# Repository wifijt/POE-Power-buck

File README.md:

# FRC PoE-switch 12 V buck-boost

A small 4-layer board that takes FRC robot power (a PDH/PDP breaker slot) and
holds a steady **12.1 V** for a Linovision **POE-Switch0504GDF**
(4-port gigabit PoE, DC 9-57 V input). It keeps the switch and its PoE cameras or
coprocessors alive when the battery sags below 9 V under heavy drive load.

| | |
|---|---|
| Board | 36.0 x 57.0 mm, 4 layers, 1.6 mm, 1 oz outer copper, rounded corners |
| Mounting | 3x M3 (3.2 mm, non-plated, no copper within 3.3 mm): top-left at (2.9, 3.4) mm, bottom corners at (3.5, 53.4) and (32.5, 53.4) mm from the top-left corner. Isolated from every net, as FRC requires for the robot frame |
| Input | 6-16 V (starts at ~5.5 V rising, stops at ~5.0 V; 16 V TVS clamp), reverse-polarity protected |
| Output | 12.1 V, 5 A continuous (60 W). Full power down to about 5.3 V input (14.9 A typ / 12.7 A min average inductor-current limit) |
| Converter | TI **TPS552882** 4-switch buck-boost (standalone, no I2C), 400 kHz |
| Connectors | 2x **WAGO 2604-3102** lever terminals (5.0 mm, up to 12 AWG / 4 mm²). Vertical wire entry; levers face the top edge |
| Indicator | Green LED = 12 V output present |

Silkscreen, left to right along the top edge: **OUT 12V (+ -)** then **IN (+ -)**.

## Wiring on the robot

* **IN**: from a PDH/PDP channel through a **10-20 A breaker**, 14-16 AWG.
* **OUT**: to the switch's PWR1 terminal (9-57 V). The switch's PoE budget is 60 W at
  12 V input (Linovision datasheet), so keep total PoE load plus the switch's own draw under about 55 W.
* The output's `-` is the board's ground, behind the reverse-polarity FET. Don't tie it to the
  input `-` anywhere else.

## Ordering (JLCPCB PCB + assembly)

1. **PCB**: upload `fab/gerbers_JLCPCB.zip` with these options:
   * Layers: **4**, thickness **1.6 mm**
   * Outer copper weight: **1 oz** (default). Inner copper weight: 0.5 oz (default)
   * Surface finish: ENIG recommended for the 0.5 mm-pitch U1 pads (HASL also works). Impedance control: off
   * **Via covering: Epoxy Filled & Capped** (a paid option on 4 layers). U1 has six 0.2 mm-drill
     vias inside its PGND and VOUT center pads; open vias there would wick solder away from the QFN.
     Set **min via hole size to 0.2 mm** (0.35 mm diameter) in the quote.

   1 oz outer copper is enough for the planned 40-55 W load (two Raspberry Pi 5s and an
   Orange Pi 5 on PoE). VIN, VOUT and GND each have a full inner plane alongside the top pour, and
   the top-only runs (GND_IN, SW1, SW2) are short: about a 10 °C rise at 12 V in, about 35 °C only
   with a sustained 6 V input. Avoid 2 oz: JLC then asks for a 0.254 mm annular ring on plated
   holes, and this board's vias have 0.15 mm (0.6/0.3) and 0.075 mm (0.35/0.2 via-in-pad) rings.
2. **Assembly**: top side only. Upload `fab/BOM_JLCPCB.csv` and `fab/CPL_JLCPCB.csv`.
   * Every line has a JLCPCB/LCSC part number, taken from jlcpcb.com part pages (Nov 2026).
     Stock changes daily, so re-run JLC's matching before you pay and swap anything out of stock
     for the same value, package and voltage rating.
   * Stock was checked against JLC's live matching on 2026-11-11. Two lines had none, so they
     were swapped: C1/C20 are now the MA35V100M6X8 polymer (C46550467, 100 µF 35 V, 30 mΩ,
     Economic OK) instead of EEH-ZK1V101XP (C454360), and R9 is now UniOhm 0402WGF2672TCE (C25876).
     Fallback for C1/C20: Lelon HBV101M1VTR-0608 hybrid (C967098). L1 (C41422303) and
     Q1-Q3 (C201632) have only a few hundred in stock.
   * Rotations were checked in JLC's placement preview (2026-11-10). C1/C20 needed 180° and
     `gen_fab.py` now applies that; U1, Q1-Q3 and D1-D3 match. Still glance at the preview: the
     magenta **+** on C1/C20 must sit on the bottom pad, next to the white silkscreen **+**.
3. **Hand-solder** J1 and J2 (WAGO 2604-3102, `fab/BOM_hand_solder.csv`) after the board
   arrives. The pads are 2.6 mm with 1.4 mm drills, two pins per pole, and are connected solid to
   the copper planes, so use a big iron tip.

## First power-up

0. Before any power, check D1 (the SMBJ16A TVS) isn't reversed: meter in diode mode, red probe on
   OUT - (board GND), black on IN +. Expect ~0.6-0.7 V; swapped probes read open (or C1 charging).
   ~0.6 V with red on IN + means D1 is backwards and would short the input.
1. Bench supply at 12 V with a 0.5 A current limit and no load. Expect 12.1 V (±2 %) and the LED on.
2. Sweep the input from 6 V to 16 V with a 1-2 A load and check the output stays at 12 V.
3. Raise the load step by step to 5 A at 12 V input, then at 7 V input. Watch the temperatures of
   L1, Q1 and Q2 (the buck-leg FETs) and U1.
4. Reverse the input briefly at a low current limit and confirm nothing conducts.

## What's in here

```
frc-poe-buckboost.kicad_pro / .kicad_sch / .kicad_pcb   KiCad 10 project
frc_poe.pretty/      TPS552882 VQFN-HR-26, WAGO 2604-3102, NexFET SON3x3 footprints
enclosure/           3D-printable case (OpenSCAD source + tray/lid STLs), see enclosure/README.md
fab/                 Gerbers + drill (zip), JLC BOM, JLC CPL, hand-solder BOM
docs/                schematic.pdf, board_top.png, board_layers.png,
                     TPS552882_datasheet_SLVSFC5.pdf (TI, Nov 2020; the design notes cite it)
scripts/             generators - design.py is the single source of truth
```

Regenerate everything after editing `scripts/design.py`. The PCB scripts need KiCad's own
Python (the one that can `import pcbnew`). Tested with KiCad 10.0.6 on macOS; the scripts also
still handle KiCad 7 on Linux (`/usr/bin/python3`, libraries in `/usr/share/kicad`). Set
`KICAD_SHARE` if the stock symbol/footprint libraries live somewhere else.

```bash
KPY=/Applications/KiCad/KiCad.app/Contents/Frameworks/Python.framework/Versions/3.9/bin/python3
KCLI=/Applications/KiCad/KiCad.app/Contents/MacOS/kicad-cli

python3 scripts/gen_footprints.py
python3 scripts/gen_sch.py
$KPY scripts/gen_pcb.py            # placement, tracks, zones (unfilled)
$KPY scripts/fill_drc.py           # reload, fill zones, save, DRC report -> drc.rpt
$KPY scripts/gen_fab.py            # BOM / CPL / hand-solder BOM

# gerbers + drill -> fab/gerbers_JLCPCB.zip
rm -f fab/gerbers/* fab/gerbers_JLCPCB.zip
$KCLI pcb export gerbers -o fab/gerbers/ --use-drill-file-origin \
  -l F.Cu,In1.Cu,In2.Cu,B.Cu,F.Paste,F.Silkscreen,B.Silkscreen,F.Mask,B.Mask,Edge.Cuts frc-poe-buckboost.kicad_pcb
$KCLI pcb export drill -o fab/gerbers/ --drill-origin plot --format excellon -u mm --excellon-separate-th frc-poe-buckboost.kicad_pcb
(cd fab/gerbers && zip -q ../gerbers_JLCPCB.zip *)

# check the schematic against design.py
$KCLI sch export netlist -o /tmp/frc.net frc-poe-buckboost.kicad_sch
python3 scripts/check_netlist.py /tmp/frc.net
```

KiCad 10 notes: the `pcbnew` scripts print harmless wxWidgets assert lines. Don't call
`pcbnew.WriteDRCReport()` from a script; it segfaults outside the GUI, which is why
`fill_drc.py` runs DRC through `kicad-cli`.

## Design notes

* **Copper**: 1 oz outer layers, 0.2 mm minimum track and clearance throughout (more than JLC's 1 oz minimum).
* **Layers**: top = parts, switch-node and power pours. Inner 1 = solid GND. Inner 2 = VOUT
  plane (left) and VIN plane (right). Bottom = GND plus the DR1H and EN traces.
* **U1 grounding** (TI SLVSFC5 sec. 10.1): three filled-and-capped vias in each of U1's center pads
  (PGND to the In1 ground plane, VOUT to the In2 VOUT plane) for heat and current. Analog ground
  (U1 AGND and MODE pins, R7, R9, C12 and C13) is its own AGND net, routed as traces and joined
  to power ground only at C14's ground terminal through net tie NT1. R4, R5 and C11 stay on the
  main ground plane.
* **Reverse polarity**: Q3 (low-side N-FET, gate from VIN through R12, 12 V zener clamp D3).
* **Values** (FB 100k/11k = 12.1 V; the reference used 102k/11.3k, FSW 49.9k, ILIM 22.1k (was 26.7k), UVLO 100k/28.7k (was 26.1k), compensation 15k + 10 nF + 100 pF, VCC 22 µF,
  6.8 µH inductor, external CSD17577Q3A buck FETs) follow two published TPS552882/TPS55288
  designs: a 12 V output stage in EwoudVV/ducktop2 and a 16 A booster in
  mikegoelzer/Homebrew-ECP5-SBC. The output bulk (100 µF hybrid + 4x 22 µF) is at least what
  the 12 V reference uses, which keeps the boost-mode right-half-plane zero well above crossover.
* **Checks done**: the schematic netlist, the PCB pad nets and `design.py` all match. KiCad DRC
  reports 0 unconnected items and 0 clearance errors. What's left is courtyard overlap between
  deliberately tight parts (hot-loop caps next to the FETs, boot cap next to U1) and silkscreen
  clipping.
* **Checked against TI's TPS552882 datasheet (SLVSFC5, Nov 2020)**: all 26 pins, the RPM0026A
  land pattern (pads match TI's example layout to <0.005 mm), and the FB, FSW, ILIM, EN/UVLO,
  MODE, DITH, VCC and bootstrap values. Two values changed as a result: R9 26.7k -> 22.1k (the
  old limit could fall to ~10.5 A, below the ~11 A needed at 6 V in / 60 W out) and R4 26.1k ->
  28.7k (the old divider could need 6.09 V to start). PG, CC and CDC may float; ISP/ISN tied to
  VOUT is TI's documented way to disable output current limiting.
* **Compensation** (15k + 10 nF + 100 pF) puts crossover at roughly 3-4 kHz, close to the
  datasheet's limit of 1/5 of the boost right-half-plane zero (~11-14 kHz at 6 V in, 5 A). It
  relies on the C20 polymer cap counting toward Cout. If bench tests show ringing in boost mode,
  drop R10 to about 12k.
* **Not yet verified**: there is no simulation and no built prototype.

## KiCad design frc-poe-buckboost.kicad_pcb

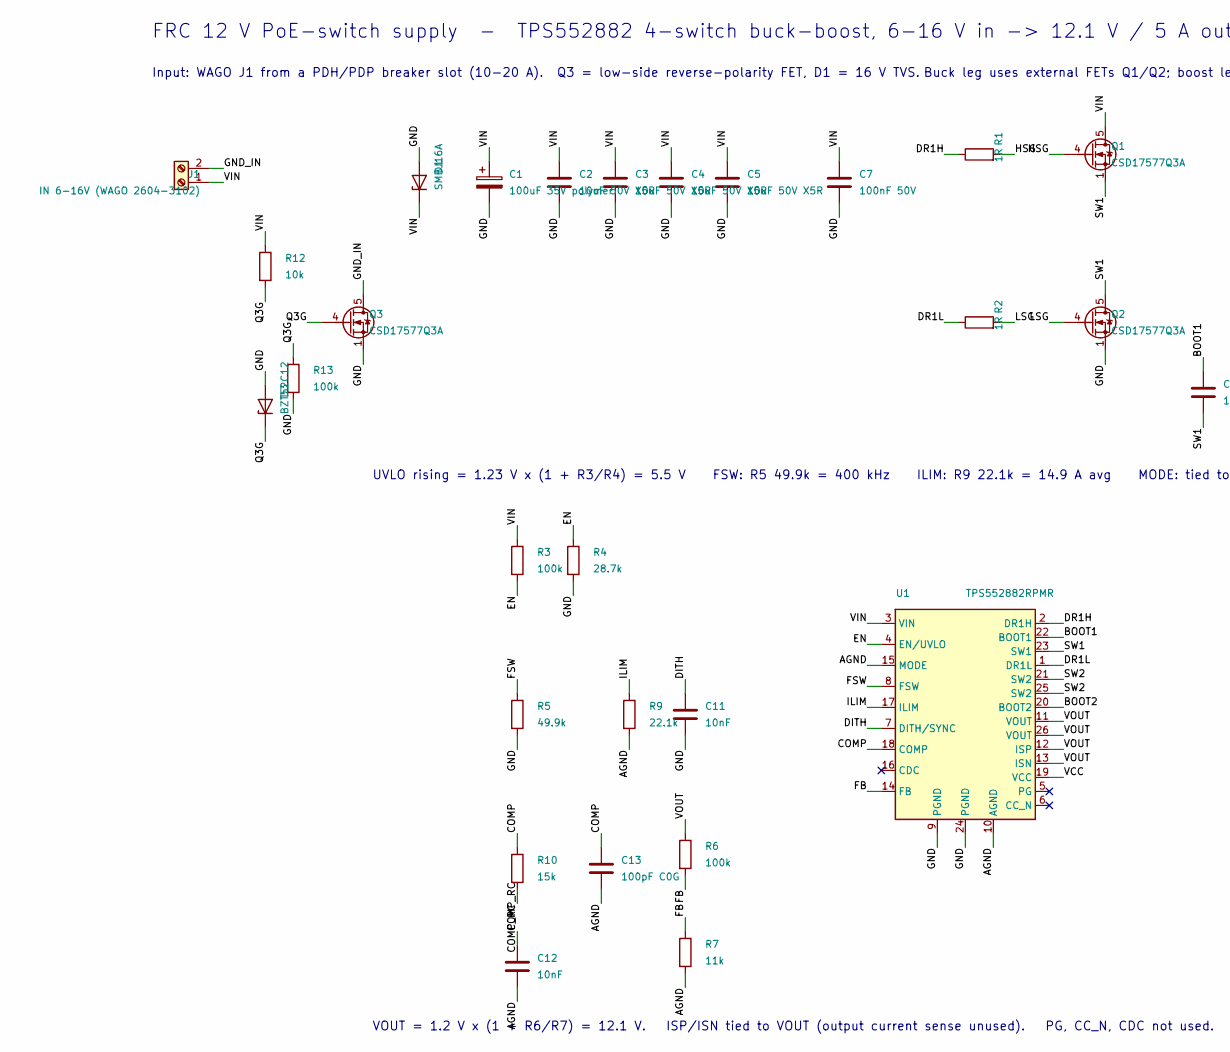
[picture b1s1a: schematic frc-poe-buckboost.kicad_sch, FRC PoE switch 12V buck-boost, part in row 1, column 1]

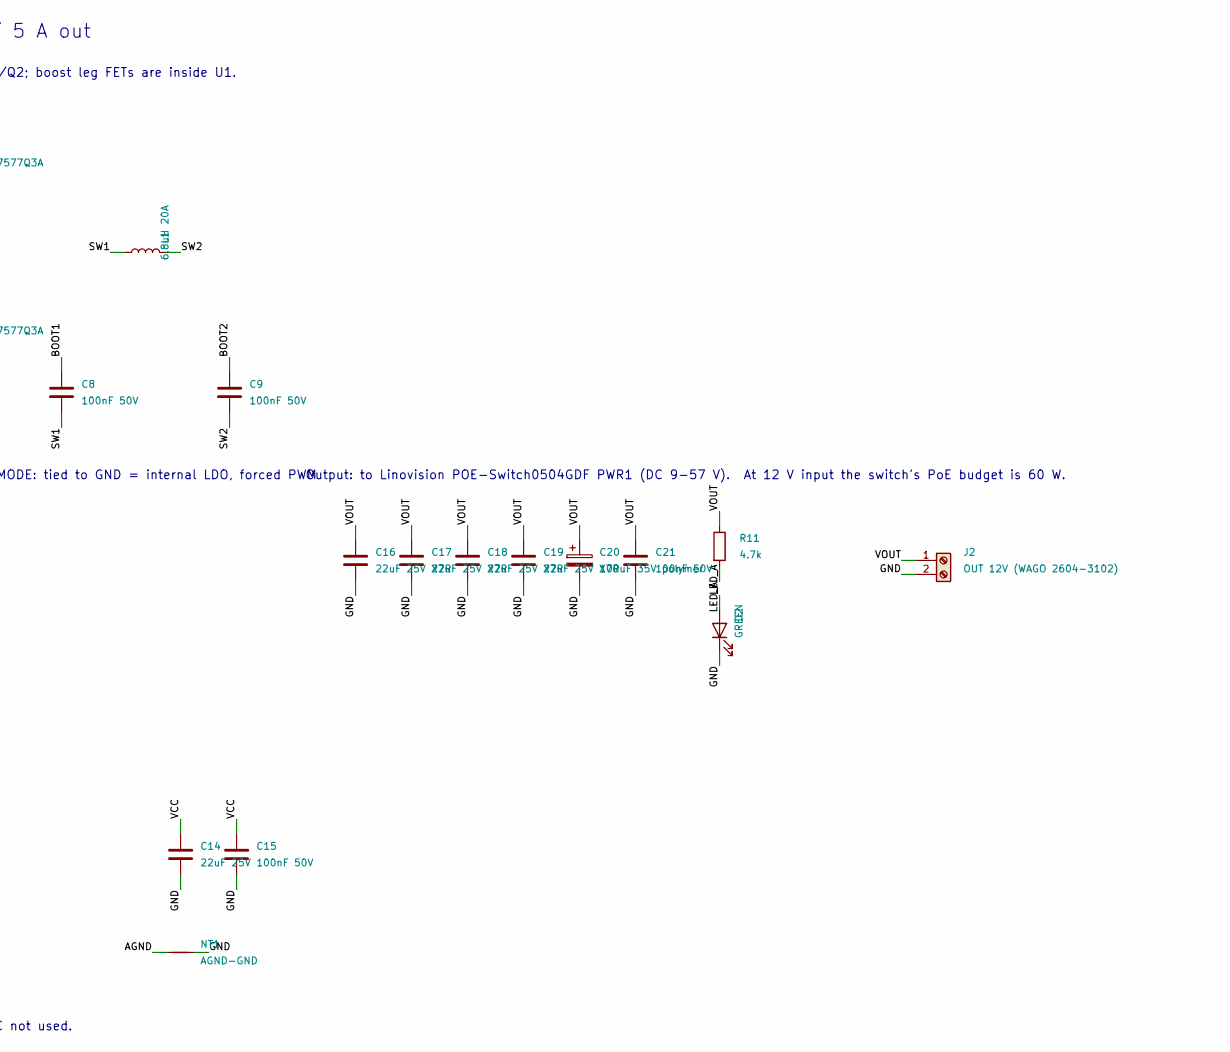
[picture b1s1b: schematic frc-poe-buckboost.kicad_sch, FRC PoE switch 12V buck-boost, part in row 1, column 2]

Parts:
C1, C20: 100uF 35V polymer; CP_Elec_6.3x7.7; MPN MA35V100M6X8; LCSC C46550467
C2, C3, C4, C5: 10uF 50V X5R; C_1206_3216Metric; MPN CL31A106KBHNNNE; LCSC C13585
C7, C8, C9, C15, C21: 100nF 50V; C_0402_1005Metric; MPN CL05B104KB54PNC; LCSC C307331
C11, C12: 10nF; C_0402_1005Metric; MPN CL05B103KB5NNNC; LCSC C15195
C13: 100pF C0G; C_0402_1005Metric; MPN 0402CG101J500NT; LCSC C1546
C14: 22uF 25V; C_1206_3216Metric; MPN CL31A226KAHNNNE; LCSC C12891
C16, C17, C18, C19: 22uF 25V X7R; C_1210_3225Metric; MPN GRM32ER71E226KE15L; LCSC C21397
D1: SMBJ16A; D_SMB; MPN SMBJ16A; LCSC C19077571
D2: GREEN; LED_0603_1608Metric; MPN KT-0603G; LCSC C12624
D3: BZT52C12; D_SOD-123; MPN BZT52C12; LCSC C19077410
J1: IN 6-16V (WAGO 2604-3102); WAGO_2604-3102_1x02_P5.00mm; MPN WAGO 2604-3102
J2: OUT 12V (WAGO 2604-3102); WAGO_2604-3102_1x02_P5.00mm; MPN WAGO 2604-3102
L1: 6.8uH 20A; L_TaiTech_TMPC1265_13.5x12.5mm; MPN ZEMS1265-6R8M; LCSC C41422303
NT1: AGND-GND; NetTie-2_SMD_Pad0.5mm
Q1, Q2, Q3: CSD17577Q3A; NexFET_SON-8_3.3x3.3mm; MPN CSD17577Q3A; LCSC C201632
R1, R2: 1R; R_0402_1005Metric; MPN 0402WGF100KTCE; LCSC C25086
R3, R6, R13: 100k; R_0402_1005Metric; MPN 0402WGF1003TCE; LCSC C25741
R4: 28.7k; R_0402_1005Metric; MPN 0402WGF2872TCE; LCSC C26972
R5: 49.9k; R_0402_1005Metric; MPN 0402WGF4992TCE; LCSC C25897
R7: 11k; R_0402_1005Metric; MPN 0402WGF1102TCE; LCSC C25749
R9: 22.1k; R_0402_1005Metric; MPN 0402WGF2212TCE; LCSC C43473
R10: 15k; R_0402_1005Metric; MPN 0402WGF1502TCE; LCSC C25756
R11: 4.7k; R_0603_1608Metric; MPN 0603WAF4701T5E; LCSC C23162
R12: 10k; R_0402_1005Metric; MPN 0402WGF1002TCE; LCSC C25744
U1: TPS552882RPMR; TI_RPM0026A_VQFN-HR-26_4x3.5mm; MPN TPS552882RPMR; LCSC C3188898

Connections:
AGND: C12.2, C13.2, NT1.1, R7.2, R9.2, U1.10 (AGND), U1.15 (MODE)
BOOT1: C8.1, U1.22 (BOOT1)
BOOT2: C9.1, U1.20 (BOOT2)
COMP: C13.1, R10.1, U1.18 (COMP)
COMP_RC: C12.1, R10.2
DITH: C11.1, U1.7 (DITH/SYNC)
DR1H: R1.1, U1.2 (DR1H)
DR1L: R2.1, U1.1 (DR1L)
EN: R3.2, R4.1, U1.4 (EN/UVLO)
FB: R6.2, R7.1, U1.14 (FB)
FSW: R5.1, U1.8 (FSW)
GND: C1.2, C2.2, C3.2, C4.2, C5.2, C7.2, C11.2, C14.2, C15.2, C16.2, C17.2, C18.2, C19.2, C20.2, C21.2, D1.2 (A), D2.1 (K), D3.2 (A), J2.2, NT1.2, Q2.1 (S), Q2.2 (S), Q2.3 (S), Q3.1 (S), Q3.2 (S), Q3.3 (S), R4.2, R5.2, R13.2, U1.9 (PGND), U1.24 (PGND)
GND_IN: J1.2, Q3.5 (D)
HSG: Q1.4 (G), R1.2
ILIM: R9.1, U1.17 (ILIM)
LED_A: D2.2 (A), R11.2
LSG: Q2.4 (G), R2.2
Q3G: D3.1 (K), Q3.4 (G), R12.2, R13.1
SW1: C8.2, L1.1, Q1.1 (S), Q1.2 (S), Q1.3 (S), Q2.5 (D), U1.23 (SW1)
SW2: C9.2, L1.2, U1.21 (SW2), U1.25 (SW2)
VCC: C14.1, C15.1, U1.19 (VCC)
VIN: C1.1, C2.1, C3.1, C4.1, C5.1, C7.1, D1.1 (K), J1.1, Q1.5 (D), R3.1, R12.1, U1.3 (VIN)
VOUT: C16.1, C17.1, C18.1, C19.1, C20.1, C21.1, J2.1, R6.1, R11.1, U1.11 (VOUT), U1.12 (ISP), U1.13 (ISN), U1.26 (VOUT)

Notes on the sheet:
FRC 12 V PoE-switch supply - TPS552882 4-switch buck-boost, 6-16 V in -> 12.1 V / 5 A out
Input: WAGO J1 from a PDH/PDP breaker slot (10-20 A). Q3 = low-side reverse-polarity FET, D1 = 16 V TVS.
Buck leg uses external FETs Q1/Q2; boost leg FETs are inside U1.
UVLO rising = 1.23 V x (1 + R3/R4) = 5.5 V FSW: R5 49.9k = 400 kHz ILIM: R9 22.1k = 14.9 A avg MODE: tied to GND = internal LDO, forced PWM
VOUT = 1.2 V x (1 + R6/R7) = 12.1 V. ISP/ISN tied to VOUT (output current sense unused). PG, CC_N, CDC not used.
Output: to Linovision POE-Switch0504GDF PWR1 (DC 9-57 V). At 12 V input the switch's PoE budget is 60 W.

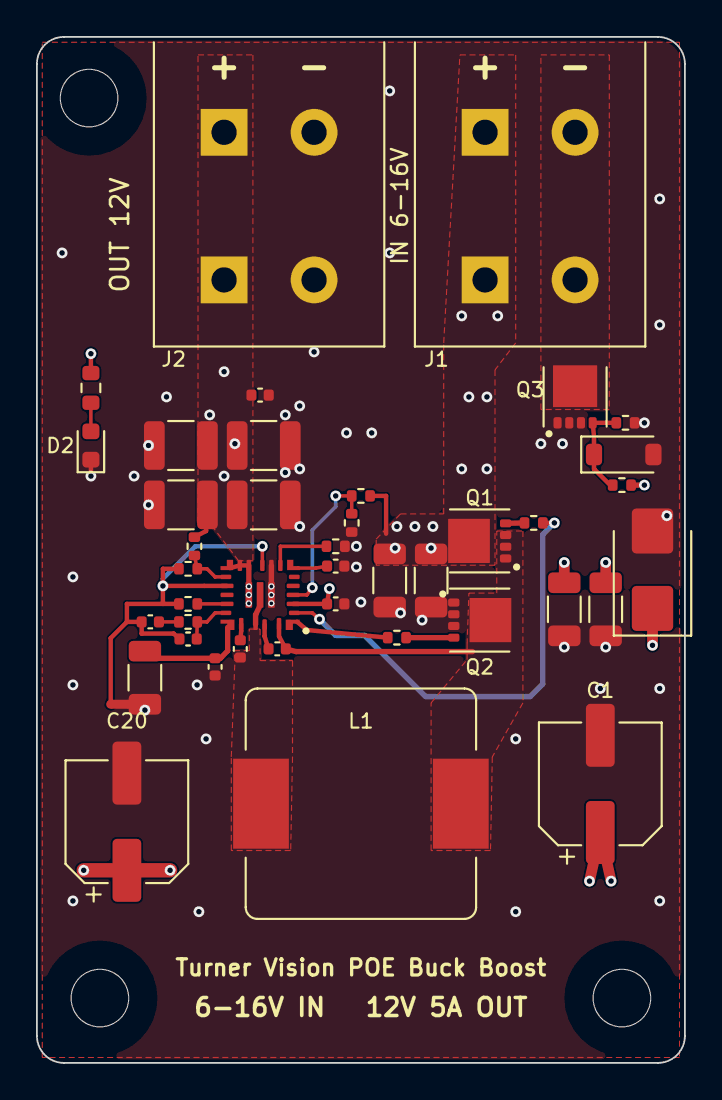
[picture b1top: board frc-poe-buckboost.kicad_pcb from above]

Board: 4 copper layers, 36.0 x 57.0 mm, 45 parts (0 on the bottom side), 23 nets.

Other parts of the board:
H1, H2, H3: MountingHole_3.2mm_M3

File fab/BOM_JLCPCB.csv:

Comment,Designator,Footprint,JLCPCB Part #,MPN,Qty
100uF 35V polymer,"C1,C20","SMD,D6.3xL7.7mm",C46550467,MA35V100M6X8,2
10uF 50V X5R,"C2,C3,C4,C5",1206,C13585,CL31A106KBHNNNE,4
100nF 50V,"C7,C8,C9,C15,C21",0402,C307331,CL05B104KB54PNC,5
10nF,"C11,C12",0402,C15195,CL05B103KB5NNNC,2
100pF C0G,C13,0402,C1546,0402CG101J500NT,1
22uF 25V,C14,1206,C12891,CL31A226KAHNNNE,1
22uF 25V X7R,"C16,C17,C18,C19",1210,C21397,GRM32ER71E226KE15L,4
SMBJ16A,D1,SMB(DO-214AA),C19077571,SMBJ16A,1
GREEN,D2,0603,C12624,KT-0603G,1
BZT52C12,D3,SOD-123,C19077410,BZT52C12,1
6.8uH 20A,L1,"SMD,13.5x12.8mm",C41422303,ZEMS1265-6R8M,1
CSD17577Q3A,"Q1,Q2,Q3",VSONP-8(3.3x3.3),C201632,CSD17577Q3A,3
1R,"R1,R2",0402,C25086,0402WGF100KTCE,2
100k,"R3,R6,R13",0402,C25741,0402WGF1003TCE,3
28.7k,R4,0402,C26972,0402WGF2872TCE,1
49.9k,R5,0402,C25897,0402WGF4992TCE,1
11k,R7,0402,C25749,0402WGF1102TCE,1
22.1k,R9,0402,C43473,0402WGF2212TCE,1
15k,R10,0402,C25756,0402WGF1502TCE,1
4.7k,R11,0603,C23162,0603WAF4701T5E,1
10k,R12,0402,C25744,0402WGF1002TCE,1
TPS552882RPMR,U1,VQFN-26-HR(4x3.5),C3188898,TPS552882RPMR,1

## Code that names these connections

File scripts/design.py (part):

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         fp=WAGO, pins={"1": "VIN", "2": "GND_IN"}, mpn="WAGO 2604-3102",
         desc="PCB terminal block, lever, 2-pole, 5.0 mm, 4 mm2 / 12 AWG", lcsc="", tht=True),
    dict(ref="J2", sym="Connector:Screw_Terminal_01x02", value="OUT 12V (WAGO 2604-3102)",
         fp=WAGO, pins={"1": "VOUT", "2": "GND"}, mpn="WAGO 2604-3102",
         desc="PCB terminal block, lever, 2-pole, 5.0 mm, 4 mm2 / 12 AWG", lcsc="", tht=True),
    # ---- reverse-polarity protection (low-side N-FET) + surge ---------------
    dict(ref="Q3", sym="Transistor_FET:CSD17577Q3A", value="CSD17577Q3A", fp=FET,
         pins={"1": "GND", "2": "GND", "3": "GND", "4": "Q3G", "5": "GND_IN"},
         lcsc="C201632", mpn="CSD17577Q3A", desc="30V N-MOSFET, SON3x3 - reverse-polarity switch"),
    dict(ref="R12", sym="Device:R", value="10k", fp=R0402, pins={"1": "VIN", "2": "Q3G"},
         lcsc="C25744", mpn="0402WGF1002TCE", desc="10k 1% 0402"),
    dict(ref="R13", sym="Device:R", value="100k", fp=R0402, pins={"1": "Q3G", "2": "GND"},
         lcsc="C25741", mpn="0402WGF1003TCE", desc="100k 1% 0402"),
    dict(ref="D3", sym="Device:D_Zener", value="BZT52C12", fp="Diode_SMD:D_SOD-123",
         pins={"1": "Q3G", "2": "GND"}, lcsc="C19077410", mpn="BZT52C12", desc="12V zener, SOD-123 - Q3 gate clamp"),
    dict(ref="D1", sym="Device:D_Zener", value="SMBJ16A", fp="Diode_SMD:D_SMB",
         pins={"1": "VIN", "2": "GND"}, lcsc="C19077571", mpn="SMBJ16A", desc="TVS 16V standoff unidirectional, SMB"),
    # ---- input capacitors ---------------------------------------------------
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         lcsc="C307331", mpn="CL05B104KB54PNC", desc="100nF 50V X7R 0402"),
    # ---- buck leg (external FETs) -------------------------------------------
    dict(ref="Q1", sym="Transistor_FET:CSD17577Q3A", value="CSD17577Q3A", fp=FET,
         pins={"1": "SW1", "2": "SW1", "3": "SW1", "4": "HSG", "5": "VIN"},
         lcsc="C201632", mpn="CSD17577Q3A", desc="30V N-MOSFET, SON3x3 - buck high side"),
    dict(ref="Q2", sym="Transistor_FET:CSD17577Q3A", value="CSD17577Q3A", fp=FET,
         pins={"1": "GND", "2": "GND", "3": "GND", "4": "LSG", "5": "SW1"},
         lcsc="C201632", mpn="CSD17577Q3A", desc="30V N-MOSFET, SON3x3 - buck low side"),
    dict(ref="R1", sym="Device:R", value="1R", fp=R0402, pins={"1": "DR1H", "2": "HSG"},
         lcsc="C25086", mpn="0402WGF100KTCE", desc="1R 1% 0402 gate resistor"),
    dict(ref="R2", sym="Device:R", value="1R", fp=R0402, pins={"1": "DR1L", "2": "LSG"},
         lcsc="C25086", mpn="0402WGF100KTCE", desc="1R 1% 0402 gate resistor"),
    dict(ref="L1", sym="Device:L", value="6.8uH 20A", fp="Inductor_SMD:L_TaiTech_TMPC1265_13.5x12.5mm",
         pins={"1": "SW1", "2": "SW2"}, lcsc="C41422303", mpn="ZEMS1265-6R8M",
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    # ---- controller -----------------------------------------------------------
    dict(ref="U1", sym="frc_poe:TPS552882", value="TPS552882RPMR",
         fp="frc_poe:TI_RPM0026A_VQFN-HR-26_4x3.5mm",
         pins={"1": "DR1L", "2": "DR1H", "3": "VIN", "4": "EN", "5": None, "6": None,
               "7": "DITH", "8": "FSW", "9": "GND", "10": "AGND", "11": "VOUT", "12": "VOUT",
               "13": "VOUT", "14": "FB", "15": "AGND", "16": None, "17": "ILIM", "18": "COMP",
               "19": "VCC", "20": "BOOT2", "21": "SW2", "22": "BOOT1", "23": "SW1",
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         lcsc="C25741", mpn="0402WGF1003TCE", desc="100k 1% 0402 UVLO top"),
    dict(ref="R4", sym="Device:R", value="28.7k", fp=R0402, pins={"1": "EN", "2": "GND"},
         lcsc="C26972", mpn="0402WGF2872TCE", desc="28.7k 1% 0402 UVLO bottom (5.5V rising typ, 5.65V max; ~5.0V falling)"),
    dict(ref="C11", sym="Device:C", value="10nF", fp=C0402, pins={"1": "DITH", "2": "GND"},
         lcsc="C15195", mpn="CL05B103KB5NNNC", desc="10nF 0402 spread-spectrum dither"),
    dict(ref="R5", sym="Device:R", value="49.9k", fp=R0402, pins={"1": "FSW", "2": "GND"},
         lcsc="C25897", mpn="0402WGF4992TCE", desc="49.9k 1% 0402 -> 400 kHz"),
    dict(ref="R6", sym="Device:R", value="100k", fp=R0402, pins={"1": "VOUT", "2": "FB"},
         lcsc="C25741", mpn="0402WGF1003TCE", desc="100k 1% 0402 FB top"),
    dict(ref="R7", sym="Device:R", value="11k", fp=R0402, pins={"1": "FB", "2": "AGND"},
         lcsc="C25749", mpn="0402WGF1102TCE", desc="11k 1% 0402 FB bottom -> 12.1 V"),
    dict(ref="R9", sym="Device:R", value="22.1k", fp=R0402, pins={"1": "ILIM", "2": "AGND"},
         lcsc="C43473", mpn="0402WGF2212TCE", desc="22.1k 1% 0402 -> 14.9 A typ (12.7 A min) avg inductor limit"),
    dict(ref="R10", sym="Device:R", value="15k", fp=R0402, pins={"1": "COMP", "2": "COMP_RC"},
         lcsc="C25756", mpn="0402WGF1502TCE", desc="15k 1% 0402 compensation"),
    dict(ref="C12", sym="Device:C", value="10nF", fp=C0402, pins={"1": "COMP_RC", "2": "AGND"},
         lcsc="C15195", mpn="CL05B103KB5NNNC", desc="10nF 50V X7R 0402 compensation"),
    dict(ref="C13", sym="Device:C", value="100pF C0G", fp=C0402, pins={"1": "COMP", "2": "AGND"},
         lcsc="C1546", mpn="0402CG101J500NT", desc="100pF 50V C0G 0402 compensation"),
    dict(ref="C14", sym="Device:C", value="22uF 25V", fp=C1206, pins={"1": "VCC", "2": "GND"},
         lcsc="C12891", mpn="CL31A226KAHNNNE", desc="22uF 25V X5R 1206 (VCC, needs >4.7uF effective)"),
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    # AGND (U1 AGND + MODE, FB/ILIM/COMP returns) meets PGND only here, at C14's GND
    # terminal (TI SLVSFC5 sec. 10.1).  R4/R5/C11 stay on the main GND plane.
    dict(ref="NT1", sym="Device:NetTie_2", value="AGND-GND", fp="NetTie:NetTie-2_SMD_Pad0.5mm",
         pins={"1": "AGND", "2": "GND"}, mpn="", lcsc="", desc="AGND/PGND star point at C14", virtual=True),
    # ---- output ---------------------------------------------------------------
    *[dict(ref=f"C{n}", sym="Device:C", value="22uF 25V X7R", fp=C1210,
           pins={"1": "VOUT", "2": "GND"}, lcsc="C21397", mpn="GRM32ER71E226KE15L", desc="22uF 25V X7R 1210")
      for n in (16, 17, 18, 19)],
    dict(ref="C20", sym="Device:C_Polarized", value="100uF 35V polymer", fp=CPOL,
         pins={"1": "VOUT", "2": "GND"}, lcsc="C46550467", mpn="MA35V100M6X8",
         desc="100uF 35V solid polymer, 30 mOhm (ESR zero ~53 kHz), 6.3x7.7 (output bulk)"),
    dict(ref="C21", sym="Device:C", value="100nF 50V", fp=C0402, pins={"1": "VOUT", "2": "GND"},
         lcsc="C307331", mpn="CL05B104KB54PNC", desc="100nF 50V X7R 0402"),
    dict(ref="R11", sym="Device:R", value="4.7k", fp=R0603, pins={"1": "VOUT", "2": "LED_A"},
         lcsc="C23162", mpn="0603WAF4701T5E", desc="4.7k 0603 LED resistor"),
    dict(ref="D2", sym="Device:LED", value="GREEN", fp="LED_SMD:LED_0603_1608Metric",
         pins={"1": "GND", "2": "LED_A"}, lcsc="C12624", mpn="KT-0603G", desc="Green LED 0603 - 12V output on"),
]

NO_CONNECT = {("U1", "5"), ("U1", "6"), ("U1", "16")}
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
